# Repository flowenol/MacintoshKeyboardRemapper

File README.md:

# MacintoshKeyboardRemapper

This is an Arduino project which allows to customize Macintosh 128k/512k/Plus M0110 keyboard layout. Currently I have remapped some of the international layout keyboard keys to match their equivalents in english versions of early Macintosh System.

Custom Eagle board and schematics have been added in case you wanted to assemble the dedicated device. There is also a simple case available for 3D printing on [tinkercad](https://www.tinkercad.com/things/eFeMwL3gJX1-mackeyboardremapperbox).

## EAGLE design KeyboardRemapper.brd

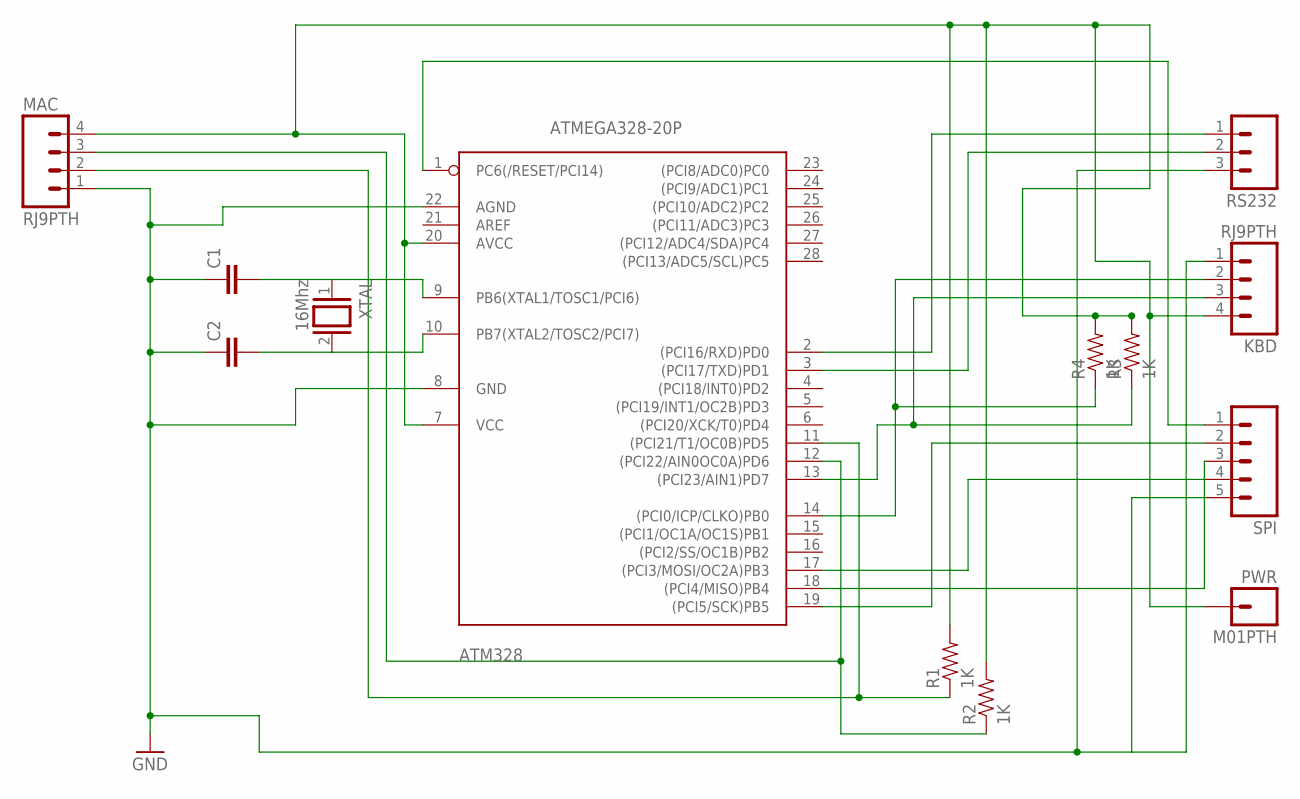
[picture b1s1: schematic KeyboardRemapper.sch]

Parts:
ATM328: ATMEGA328-20P; DIL28-3
C1, C2: CAPPTH2; CAP-PTH-SMALL2
KBD: RJ9PTH; RJ9
MAC: RJ9PTH; RJ9
PWR: M01PTH; 1X01
R1, R2, R3, R4: 1K; AXIAL-0.3
RS232: M03PTH; 1X03
SPI: M05PTH; 1X05
XTAL: 16Mhz; QS

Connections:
GND: ATM328.8 (GND), ATM328.22 (AGND), C1.1, C2.1, KBD.1, MAC.1, RS232.3, SPI.5
KBD_CLK: ATM328.14 ((PCI0/ICP/CLKO)PB0), KBD.2, R4.P$1 (1)
KBD_DATA: ATM328.13 ((PCI23/AIN1)PD7), KBD.3, R3.P$1 (1)
MAC_CLK: ATM328.11 ((PCI21/T1/OC0B)PD5), MAC.2, R1.P$1 (1)
MAC_DATA: ATM328.12 ((PCI22/AIN0OC0A)PD6), MAC.3, R2.P$1 (1)
MISO: ATM328.18 ((PCI4/MISO)PB4), SPI.3
MOSI: ATM328.17 ((PCI3/MOSI/OC2A)PB3), SPI.4
unnamed: ATM328.10 (PB7(XTAL2/TOSC2/PCI7)), C2.2, XTAL.2
unnamed: ATM328.9 (PB6(XTAL1/TOSC1/PCI6)), C1.2, XTAL.1
unnamed: ATM328.2 ((PCI16/RXD)PD0), RS232.1
unnamed: ATM328.3 ((PCI17/TXD)PD1), RS232.2
PWR: ATM328.7 (VCC), ATM328.20 (AVCC), KBD.4, MAC.4, PWR.1, R1.P$2 (2), R2.P$2 (2), R3.P$2 (2), R4.P$2 (2)
RST: ATM328.1 (PC6(/RESET/PCI14)), SPI.1
SCK: ATM328.19 ((PCI5/SCK)PB5), SPI.2

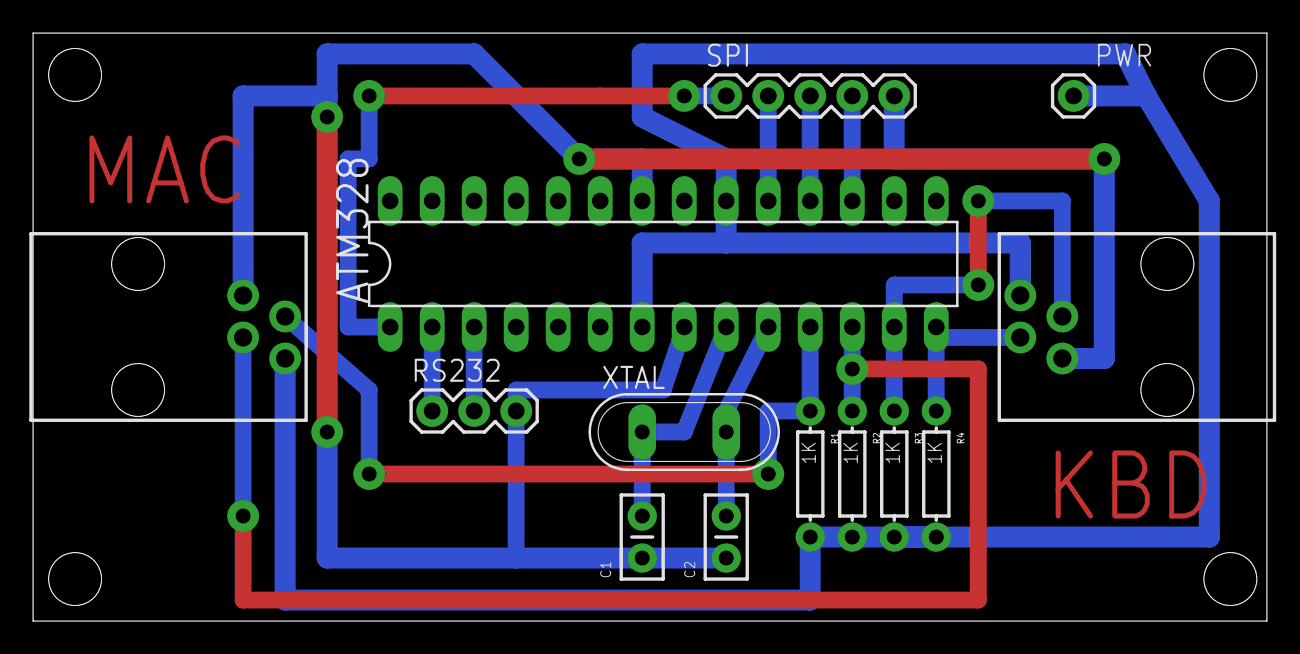
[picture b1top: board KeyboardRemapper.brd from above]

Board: 2 copper layers, 74.6 x 35.5 mm, 13 parts (0 on the bottom side), 14 nets.

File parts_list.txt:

Partlist

Exported from KeyboardRemapper.sch at 22/11/2019 23:16

EAGLE Version 7.2.0 Copyright (c) 1988-2014 CadSoft

Assembly variant: 

Part     Value          Device        Package        Library   Sheet

ATM328   ATMEGA328-20P  ATMEGA328-20P DIL28-3        atmega328 1
C1       22pF           CAPPTH2       CAP-PTH-SMALL2 SparkFun  1
C2       22pF           CAPPTH2       CAP-PTH-SMALL2 SparkFun  1
KBD      RJ9PTH         RJ9PTH        RJ9            SparkFun  1
MAC      RJ9PTH         RJ9PTH        RJ9            SparkFun  1
PWR      M01PTH         M01PTH        1X01           SparkFun  1
R1       1K             RESISTORPTH1  AXIAL-0.3      SparkFun  1
R2       1K             RESISTORPTH1  AXIAL-0.3      SparkFun  1
R3       1K             RESISTORPTH1  AXIAL-0.3      SparkFun  1
R4       1K             RESISTORPTH1  AXIAL-0.3      SparkFun  1
RS232                   M03PTH        1X03           SparkFun  1
SPI                     M05PTH        1X05           SparkFun  1
XTAL     16Mhz          XTAL/S        QS             special   1

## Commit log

2019-09-30 main file renamed
2019-09-30 pins swap
2019-10-16 keyboard pin swap
2019-10-30 README.md
2021-03-01 Schematics, board, parts list and case project added.
